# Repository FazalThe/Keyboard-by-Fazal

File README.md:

# Custom Wireless Mechanical Keyboard (Pico W)

A custom-designed **wireless mechanical keyboard** built around the **Raspberry Pi Pico W**, featuring a hand-wired key matrix, rotary encoders, OLED display, rechargeable battery support, and a fully custom 3D-printed case.

The **Layout** is custome made by me

---

## 📸 Project Overview

### Top Plate

### Case (Bottom Shell)

### Key Layout

### Electrical Schematic

---

## 🧩 Bill of Materials 
### Core Electronics
- Raspberry Pi Pico W ×1  
- Mechanical key switches ×78  
- Keyboard diodes ×81  
- SK6812 MINI RGB LEDs ×7  
- Rotary encoders ×2  
- 0.91″ OLED display ×1  
- MCP73831 Li-ion charger ×1  
- TVS ESD protection IC ×1  
- Fuse (500 mA) ×1  
- Resistors (4.7 kΩ ×2, 2 kΩ ×1)  

### Power & Connectivity
- Protected Li-Po battery ×1  
- JST 2-pin battery connector ×1  
- USB connector / header ×1  
- SS12F15 slide switch ×1  

### Mechanical & Assembly
- MX keycaps ×78 (look layout for reference)  
- Rotary encoder caps ×2  
- Copper wire (for hand wiring)  
- Solder board / perfboard  
- M3 × 20 mm screws ×8  
- M3 heat-set inserts ×8  

---

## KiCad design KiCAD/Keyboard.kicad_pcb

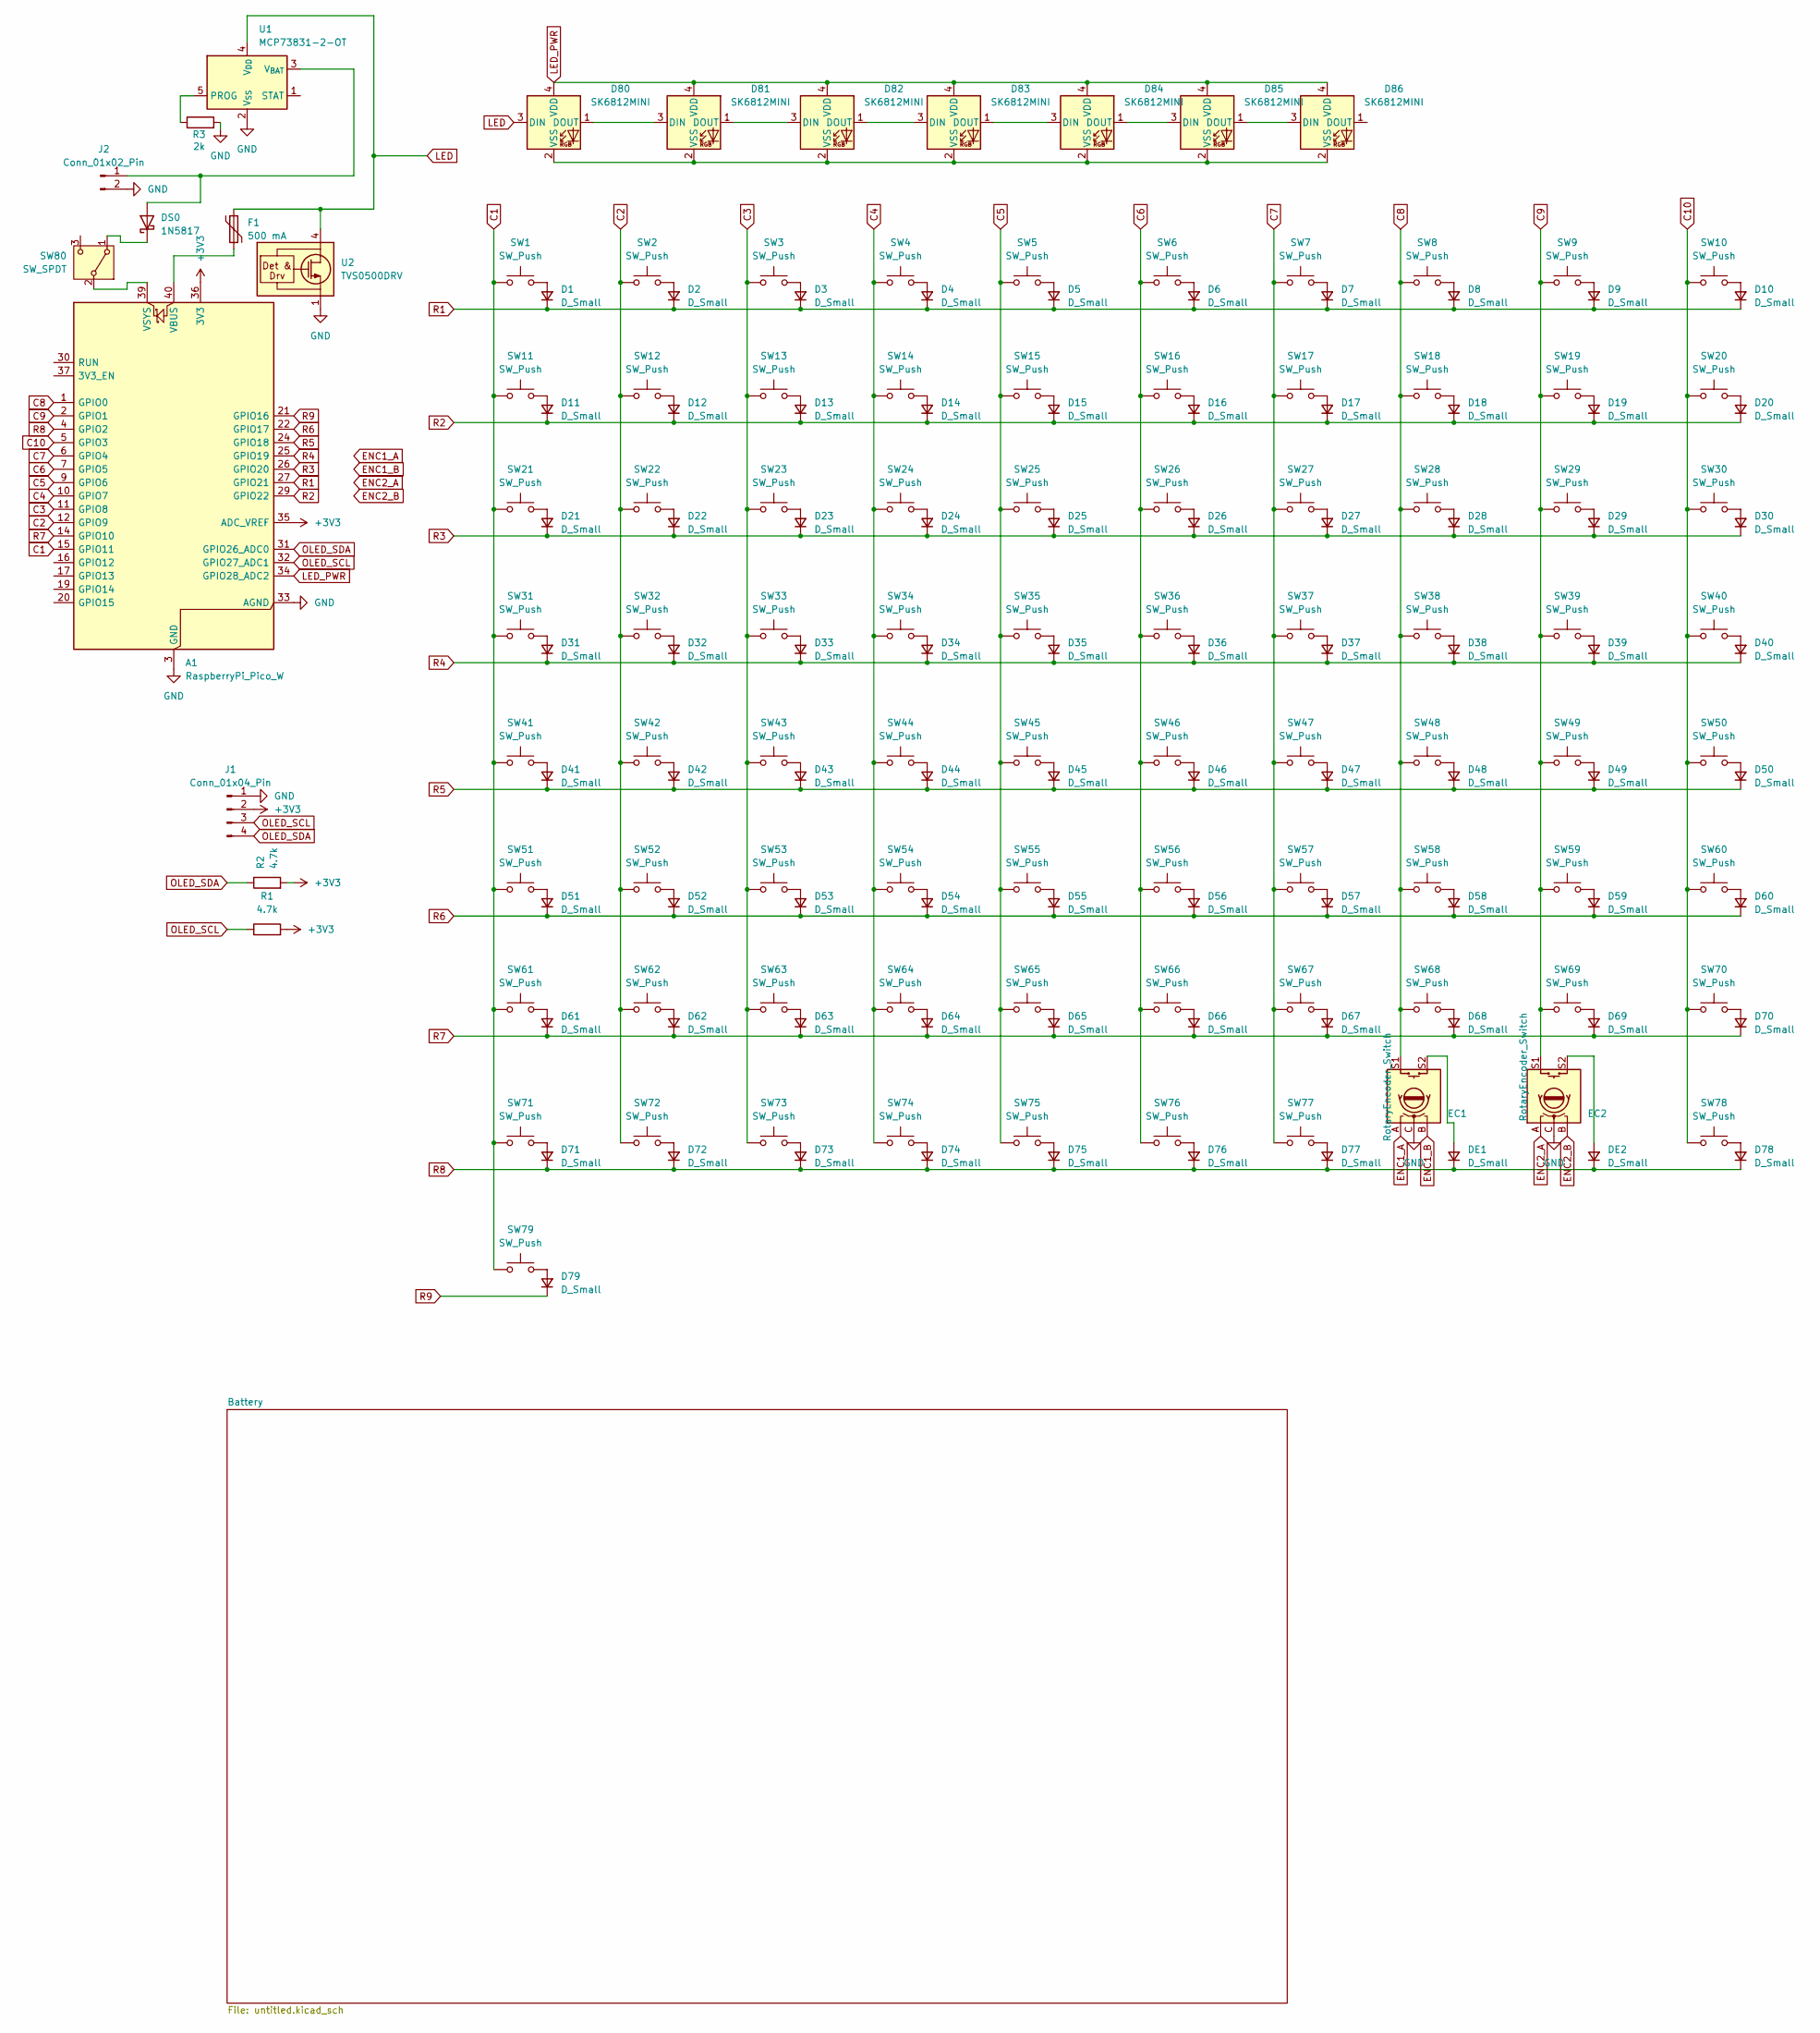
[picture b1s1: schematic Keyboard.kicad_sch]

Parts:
A1: RaspberryPi_Pico_W; RaspberryPi_Pico_W_SMD_HandSolder
D1, D2, D3, D4, D5, D6, D7, D8, D9, D10, D11, D12, D13, D14, D15, D16, D17, D18, D19, D20, D21, D22, D23, D24, D25, D26, D27, D28, D29, D30, D31, D32, D33, D34, D35, D36, D37, D38, D39, D40, D41, D42, D43, D44, D45, D46, D47, D48, D49, D50, D51, D52, D53, D54, D55, D56, D57, D58, D59, D60, D61, D62, D63, D64, D65, D66, D67, D68, D69, D70, D71, D72, D73, D74, D75, D76, D77, D78, D79: D_Small; D_SOD-123
D80, D81, D82, D83, D84, D85, D86: SK6812MINI; LED_SK6812MINI_PLCC4_3.5x3.5mm_P1.75mm
DE1, DE2: D_Small; D_SOD-123
DS0: 1N5817; D_DO-41_SOD81_P10.16mm_Horizontal
EC1, EC2: RotaryEncoder_Switch; RotaryEncoder_Alps_EC11E-Switch_Vertical_H20mm
F1: 500 mA; Fuse_1206_3216Metric_Pad1.42x1.75mm_HandSolder
J1: Conn_01x04_Pin; PinSocket_1x04_P1.00mm_Vertical_SMD_Pin1Right
J2: Conn_01x02_Pin; JST_PH_S2B-PH-K_1x02_P2.00mm_Horizontal
R1, R2: 4.7k; R_0805_2012Metric_Pad1.20x1.40mm_HandSolder
R3: 2k; R_0805_2012Metric_Pad1.20x1.40mm_HandSolder
SW1, SW2, SW3, SW4, SW5, SW6, SW7, SW8, SW9, SW10, SW11, SW12, SW13, SW14, SW15, SW16, SW17, SW18, SW19, SW20, SW21, SW22, SW23, SW24, SW25, SW26, SW27, SW28, SW29, SW30, SW31, SW32, SW33, SW34, SW35, SW36, SW37, SW38, SW39, SW40, SW41, SW42, SW43, SW44, SW45, SW46, SW47, SW48, SW49, SW50, SW51, SW52, SW53, SW54, SW55, SW56, SW57, SW58, SW59, SW60, SW61, SW62, SW63, SW64, SW65, SW66, SW67, SW68, SW69, SW70, SW71, SW72, SW73, SW74, SW75, SW76, SW77, SW78: SW_Push; SW_Cherry_MX_1.00u_PCB
SW79: SW_Push; SW_SPST_PTS645Sx43SMTR92
SW80: SW_SPDT; SW_SPDT_PCM12
U1: MCP73831-2-OT; SOT-23-5
U2: TVS0500DRV; WSON-6-1EP_2x2mm_P0.65mm_EP1x1.6mm

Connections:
+3V3: A1.35 (ADC_VREF), A1.36 (3V3), J1.2, R1.2, R2.2
C1: A1.15 (GPIO11), SW1.1, SW11.1, SW21.1, SW31.1, SW41.1, SW51.1, SW61.1, SW71.1, SW79.1
C2: A1.12 (GPIO9), SW2.1, SW12.1, SW22.1, SW32.1, SW42.1, SW52.1, SW62.1, SW72.1
C3: A1.11 (GPIO8), SW3.1, SW13.1, SW23.1, SW33.1, SW43.1, SW53.1, SW63.1, SW73.1
C4: A1.10 (GPIO7), SW4.1, SW14.1, SW24.1, SW34.1, SW44.1, SW54.1, SW64.1, SW74.1
C5: A1.9 (GPIO6), SW5.1, SW15.1, SW25.1, SW35.1, SW45.1, SW55.1, SW65.1, SW75.1
C6: A1.7 (GPIO5), SW6.1, SW16.1, SW26.1, SW36.1, SW46.1, SW56.1, SW66.1, SW76.1
C7: A1.6 (GPIO4), SW7.1, SW17.1, SW27.1, SW37.1, SW47.1, SW57.1, SW67.1, SW77.1
C8: A1.1 (GPIO0), EC1.S1, SW8.1, SW18.1, SW28.1, SW38.1, SW48.1, SW58.1, SW68.1
C9: A1.2 (GPIO1), EC2.S1, SW9.1, SW19.1, SW29.1, SW39.1, SW49.1, SW59.1, SW69.1
C10: A1.5 (GPIO3), SW10.1, SW20.1, SW30.1, SW40.1, SW50.1, SW60.1, SW70.1, SW78.1
ENC1_A: EC1.A
ENC1_B: EC1.B
ENC2_A: EC2.A
ENC2_B: EC2.B
GND: A1.3 (GND), A1.8 (GND), A1.13 (GND), A1.18 (GND), A1.23 (GND), A1.28 (GND), A1.33 (AGND), A1.38 (GND), EC1.C, EC2.C, J1.1, J2.2, R3.2, U1.2 (V_{SS}), U2.1 (GND), U2.2 (GND), U2.3 (GND), U2.7 (GND)
unnamed: A1.40 (VBUS), F1.2
unnamed: A1.39 (VSYS), SW80.2 (B)
unnamed: D1.2 (A), SW1.2
unnamed: D2.2 (A), SW2.2
unnamed: D3.2 (A), SW3.2
unnamed: D4.2 (A), SW4.2
unnamed: D5.2 (A), SW5.2
unnamed: D6.2 (A), SW6.2
unnamed: D7.2 (A), SW7.2
unnamed: D8.2 (A), SW8.2
unnamed: D9.2 (A), SW9.2
unnamed: D10.2 (A), SW10.2
unnamed: D11.2 (A), SW11.2
unnamed: D12.2 (A), SW12.2
unnamed: D13.2 (A), SW13.2
unnamed: D14.2 (A), SW14.2
unnamed: D15.2 (A), SW15.2
unnamed: D16.2 (A), SW16.2
unnamed: D17.2 (A), SW17.2
unnamed: D18.2 (A), SW18.2
unnamed: D19.2 (A), SW19.2
unnamed: D20.2 (A), SW20.2
unnamed: D21.2 (A), SW21.2
unnamed: D22.2 (A), SW22.2
unnamed: D23.2 (A), SW23.2
unnamed: D24.2 (A), SW24.2
unnamed: D25.2 (A), SW25.2
unnamed: D26.2 (A), SW26.2
unnamed: D27.2 (A), SW27.2
unnamed: D28.2 (A), SW28.2
unnamed: D29.2 (A), SW29.2
unnamed: D30.2 (A), SW30.2
unnamed: D31.2 (A), SW31.2
unnamed: D32.2 (A), SW32.2
unnamed: D33.2 (A), SW33.2
unnamed: D34.2 (A), SW34.2
unnamed: D35.2 (A), SW35.2
unnamed: D36.2 (A), SW36.2
unnamed: D37.2 (A), SW37.2
unnamed: D38.2 (A), SW38.2
unnamed: D39.2 (A), SW39.2
unnamed: D40.2 (A), SW40.2
unnamed: D41.2 (A), SW41.2
unnamed: D42.2 (A), SW42.2
unnamed: D43.2 (A), SW43.2
unnamed: D44.2 (A), SW44.2
unnamed: D45.2 (A), SW45.2
unnamed: D46.2 (A), SW46.2
unnamed: D47.2 (A), SW47.2
unnamed: D48.2 (A), SW48.2
unnamed: D49.2 (A), SW49.2
unnamed: D50.2 (A), SW50.2
unnamed: D51.2 (A), SW51.2
unnamed: D52.2 (A), SW52.2
unnamed: D53.2 (A), SW53.2
unnamed: D54.2 (A), SW54.2
unnamed: D55.2 (A), SW55.2
unnamed: D56.2 (A), SW56.2
unnamed: D57.2 (A), SW57.2
unnamed: D58.2 (A), SW58.2
unnamed: D59.2 (A), SW59.2
unnamed: D60.2 (A), SW60.2
unnamed: D61.2 (A), SW61.2
unnamed: D62.2 (A), SW62.2
unnamed: D63.2 (A), SW63.2
unnamed: D64.2 (A), SW64.2
unnamed: D65.2 (A), SW65.2
unnamed: D66.2 (A), SW66.2
unnamed: D67.2 (A), SW67.2
unnamed: D68.2 (A), SW68.2
unnamed: D69.2 (A), SW69.2
unnamed: D70.2 (A), SW70.2
unnamed: D71.2 (A), SW71.2
unnamed: D72.2 (A), SW72.2
unnamed: D73.2 (A), SW73.2
unnamed: D74.2 (A), SW74.2
unnamed: D75.2 (A), SW75.2
unnamed: D76.2 (A), SW76.2
unnamed: D77.2 (A), SW77.2
unnamed: D78.2 (A), SW78.2
unnamed: D79.2 (A), SW79.2
unnamed: D80.1 (DOUT), D81.3 (DIN)
unnamed: D80.2 (VSS), D81.2 (VSS), D82.2 (VSS), D83.2 (VSS), D84.2 (VSS), D85.2 (VSS), D86.2 (VSS)
unnamed: A1.34 (GPIO28_ADC2), D80.4 (VDD), D81.4 (VDD), D82.4 (VDD), D83.4 (VDD), D84.4 (VDD), D85.4 (VDD), D86.4 (VDD)
unnamed: D81.1 (DOUT), D82.3 (DIN)
unnamed: D82.1 (DOUT), D83.3 (DIN)
unnamed: D83.1 (DOUT), D84.3 (DIN)
unnamed: D84.1 (DOUT), D85.3 (DIN)
unnamed: D85.1 (DOUT), D86.3 (DIN)
unnamed: DE1.2 (A), EC1.S2
unnamed: DE2.2 (A), EC2.S2
unnamed: DS0.2 (A), J2.1, U1.3 (V_{BAT})
unnamed: DS0.1 (K), SW80.1 (A)
unnamed: R3.1, U1.5 (PROG)
unnamed: D80.3 (DIN), F1.1, U1.4 (V_{DD}), U2.4 (IN), U2.5 (IN), U2.6 (IN)
OLED_SCL: A1.32 (GPIO27_ADC1), J1.3, R1.1
OLED_SDA: A1.31 (GPIO26_ADC0), J1.4, R2.1
R1: A1.27 (GPIO21), D1.1 (K), D2.1 (K), D3.1 (K), D4.1 (K), D5.1 (K), D6.1 (K), D7.1 (K), D8.1 (K), D9.1 (K), D10.1 (K)
R2: A1.29 (GPIO22), D11.1 (K), D12.1 (K), D13.1 (K), D14.1 (K), D15.1 (K), D16.1 (K), D17.1 (K), D18.1 (K), D19.1 (K), D20.1 (K)
R3: A1.26 (GPIO20), D21.1 (K), D22.1 (K), D23.1 (K), D24.1 (K), D25.1 (K), D26.1 (K), D27.1 (K), D28.1 (K), D29.1 (K), D30.1 (K)
R4: A1.25 (GPIO19), D31.1 (K), D32.1 (K), D33.1 (K), D34.1 (K), D35.1 (K), D36.1 (K), D37.1 (K), D38.1 (K), D39.1 (K), D40.1 (K)
R5: A1.24 (GPIO18), D41.1 (K), D42.1 (K), D43.1 (K), D44.1 (K), D45.1 (K), D46.1 (K), D47.1 (K), D48.1 (K), D49.1 (K), D50.1 (K)
R6: A1.22 (GPIO17), D51.1 (K), D52.1 (K), D53.1 (K), D54.1 (K), D55.1 (K), D56.1 (K), D57.1 (K), D58.1 (K), D59.1 (K), D60.1 (K)
R7: A1.14 (GPIO10), D61.1 (K), D62.1 (K), D63.1 (K), D64.1 (K), D65.1 (K), D66.1 (K), D67.1 (K), D68.1 (K), D69.1 (K), D70.1 (K)
R8: A1.4 (GPIO2), D71.1 (K), D72.1 (K), D73.1 (K), D74.1 (K), D75.1 (K), D76.1 (K), D77.1 (K), D78.1 (K), DE1.1 (K), DE2.1 (K)
R9: A1.21 (GPIO16), D79.1 (K)

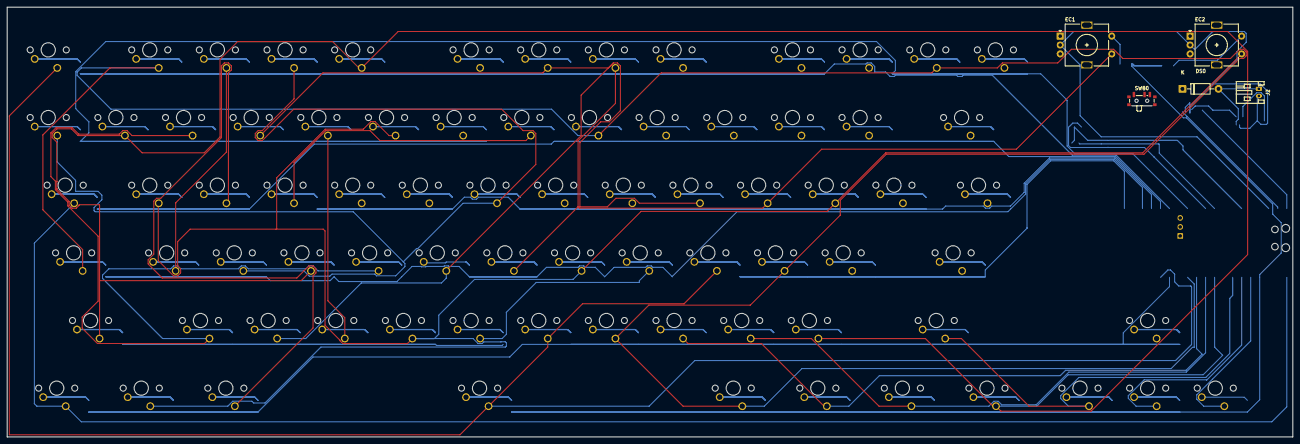
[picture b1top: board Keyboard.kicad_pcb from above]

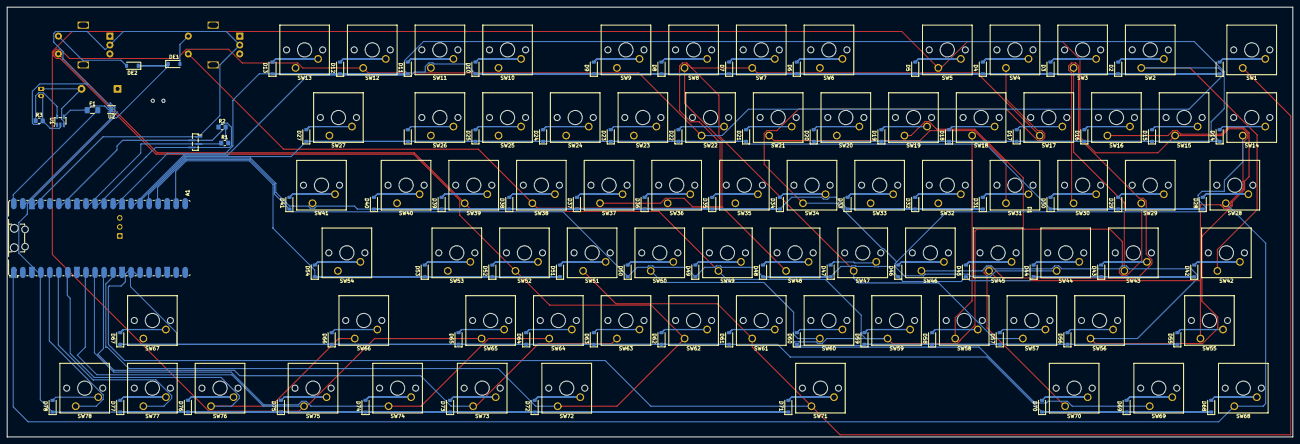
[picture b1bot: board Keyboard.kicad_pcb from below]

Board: 2 copper layers, 362.0 x 121.0 mm, 171 parts (166 on the bottom side), 108 nets.

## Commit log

2025-12-16 Revise README with detailed project information
    Expanded project description and added detailed sections including project overview, bill of materials, assembly notes, and repository structure.
2026-02-05 Update keyboard description and remove assembly notes
    Removed assembly notes section and updated keyboard description.
2026-02-20 Update README with custom layout information
    Added a note about the custom layout of the keyboard.
2026-03-31 Update images and revise Bill of Materials section
2026-03-31 Update bottom shell image in README
